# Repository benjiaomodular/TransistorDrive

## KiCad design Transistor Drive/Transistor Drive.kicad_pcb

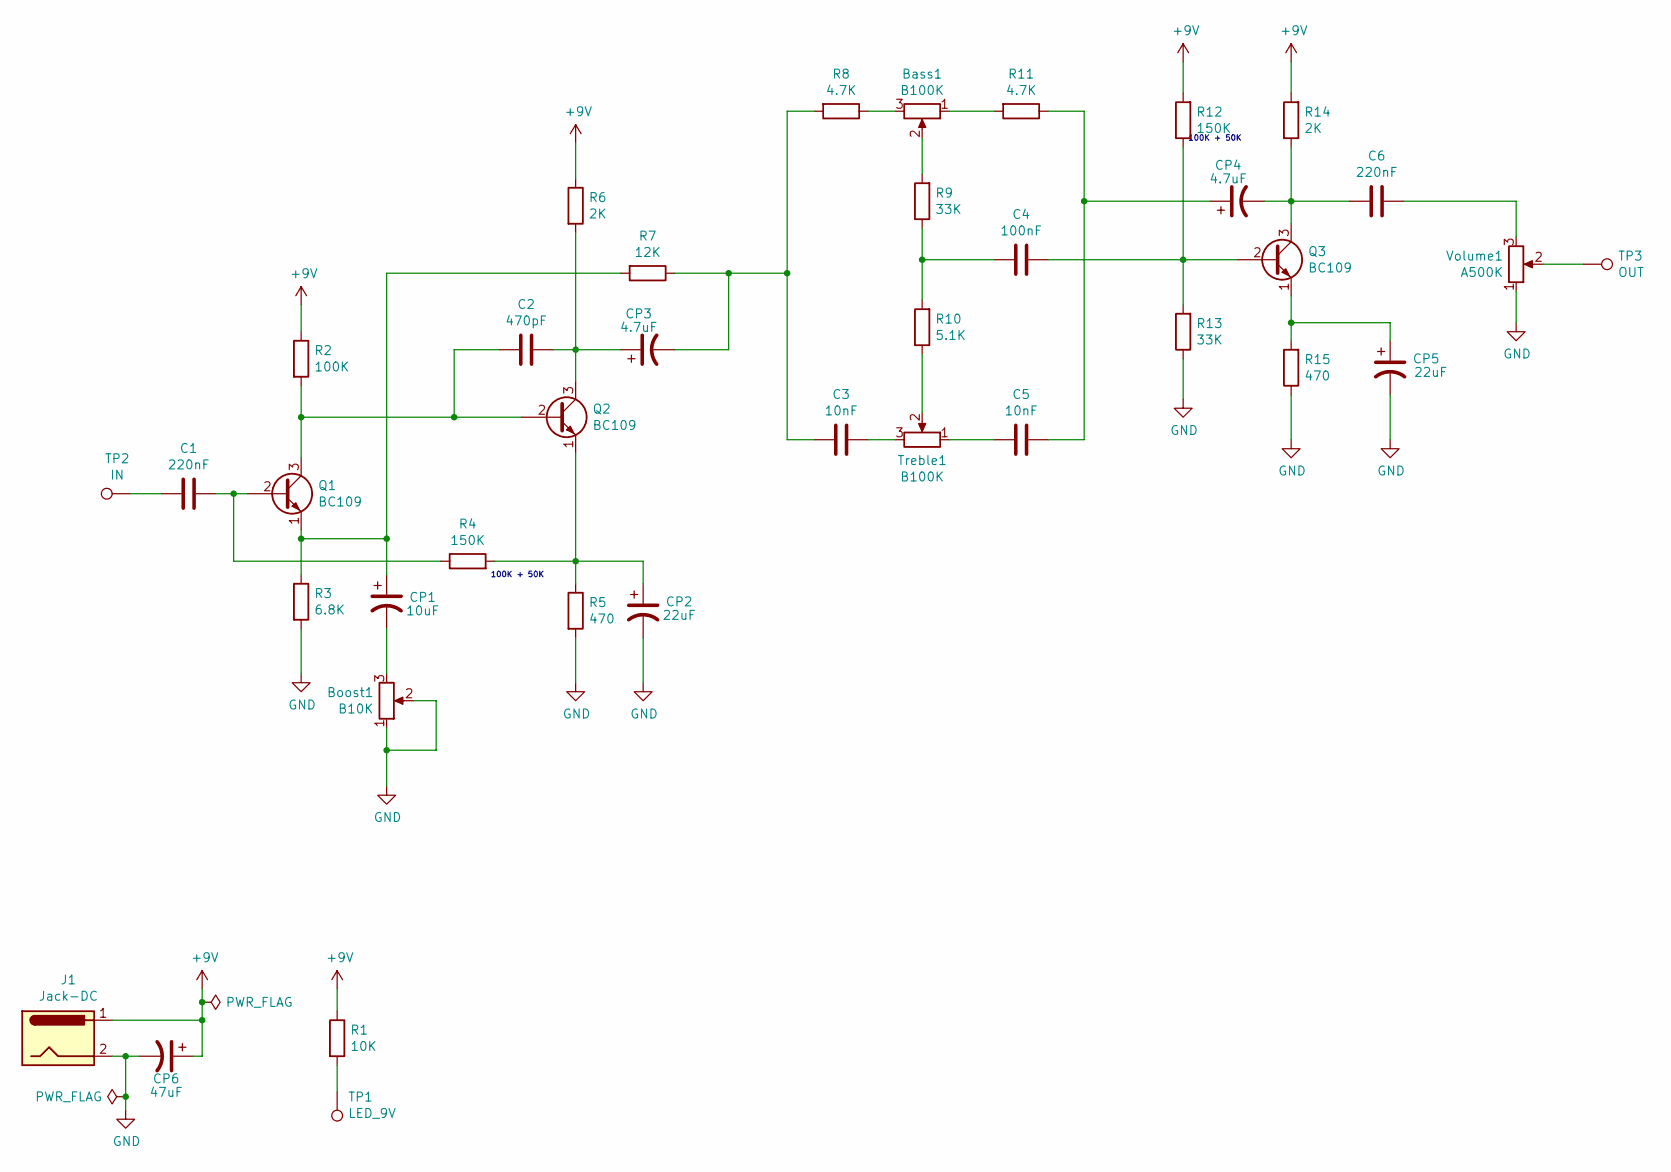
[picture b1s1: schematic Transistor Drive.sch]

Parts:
Bass1: B100K; SolderWire-0.5sqmm_1x03_P4.8mm_D0.9mm_OD2.3mm
Boost1: B10K; SolderWire-0.5sqmm_1x03_P4.8mm_D0.9mm_OD2.3mm
C1, C6: 220nF; C_Rect_L7.2mm_W2.5mm_P5.00mm_FKS2_FKP2_MKS2_MKP2
C2: 470pF; C_Rect_L7.2mm_W2.5mm_P5.00mm_FKS2_FKP2_MKS2_MKP2
C3, C5: 10nF; C_Rect_L7.2mm_W2.5mm_P5.00mm_FKS2_FKP2_MKS2_MKP2
C4: 100nF; C_Rect_L7.2mm_W2.5mm_P5.00mm_FKS2_FKP2_MKS2_MKP2
CP1: 10uF; CP_Radial_D4.0mm_P2.00mm
CP2, CP5: 22uF; CP_Radial_D4.0mm_P2.00mm
CP3, CP4: 4.7uF; CP_Radial_D4.0mm_P2.00mm
CP6: 47uF; CP_Radial_D4.0mm_P2.00mm
J1: Jack-DC; SolderWire-0.5sqmm_1x02_P4.8mm_D0.9mm_OD2.3mm
Q1, Q2, Q3: BC109; TO-18-3
R1: 10K; R_Axial_DIN0207_L6.3mm_D2.5mm_P7.62mm_Horizontal
R2: 100K; R_Axial_DIN0207_L6.3mm_D2.5mm_P7.62mm_Horizontal
R3: 6.8K; R_Axial_DIN0207_L6.3mm_D2.5mm_P7.62mm_Horizontal
R4, R12: 150K; R_Axial_DIN0207_L6.3mm_D2.5mm_P7.62mm_Horizontal
R5, R15: 470; R_Axial_DIN0207_L6.3mm_D2.5mm_P7.62mm_Horizontal
R6, R14: 2K; R_Axial_DIN0207_L6.3mm_D2.5mm_P7.62mm_Horizontal
R7: 12K; R_Axial_DIN0207_L6.3mm_D2.5mm_P7.62mm_Horizontal
R8, R11: 4.7K; R_Axial_DIN0207_L6.3mm_D2.5mm_P7.62mm_Horizontal
R9, R13: 33K; R_Axial_DIN0207_L6.3mm_D2.5mm_P7.62mm_Horizontal
R10: 5.1K; R_Axial_DIN0207_L6.3mm_D2.5mm_P7.62mm_Horizontal
TP1: LED_9V; SolderWire-0.5sqmm_1x01_D0.9mm_OD2.3mm
TP2: IN; SolderWire-0.5sqmm_1x01_D0.9mm_OD2.3mm
TP3: OUT; SolderWire-0.5sqmm_1x01_D0.9mm_OD2.3mm
Treble1: B100K; SolderWire-0.5sqmm_1x03_P4.8mm_D0.9mm_OD2.3mm
Volume1: A500K; SolderWire-0.5sqmm_1x03_P4.8mm_D0.9mm_OD2.3mm

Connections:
+9V: CP6.1, J1.1, R1.1, R2.1, R6.1, R12.2, R14.2
GND: Boost1.1, Boost1.2, CP2.2, CP5.2, CP6.2, J1.2, R3.2, R5.2, R13.1, R15.1, Volume1.1
unnamed: Bass1.1, R11.2
unnamed: Bass1.2, R9.2
unnamed: Bass1.3, R8.1
unnamed: Boost1.3, CP1.2
unnamed: C1.1, Q1.2 (B), R4.1
unnamed: C1.2, TP2.1
unnamed: C2.1, CP3.1, Q2.3 (C), R6.2
unnamed: C2.2, Q1.3 (C), Q2.2 (B), R2.2
unnamed: C3.1, Treble1.3
unnamed: C3.2, CP3.2, R7.1, R8.2
unnamed: C4.1, Q3.2 (B), R12.1, R13.2
unnamed: C4.2, R9.1, R10.2
unnamed: C5.1, CP4.1, R11.1
unnamed: C5.2, Treble1.1
unnamed: C6.1, Volume1.3
unnamed: C6.2, CP4.2, Q3.3 (C), R14.1
unnamed: CP1.1, Q1.1 (E), R3.1, R7.2
unnamed: CP2.1, Q2.1 (E), R4.2, R5.1
unnamed: CP5.1, Q3.1 (E), R15.2
unnamed: R1.2, TP1.1
unnamed: R10.1, Treble1.2
unnamed: TP3.1, Volume1.2

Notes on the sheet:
100K + 50K

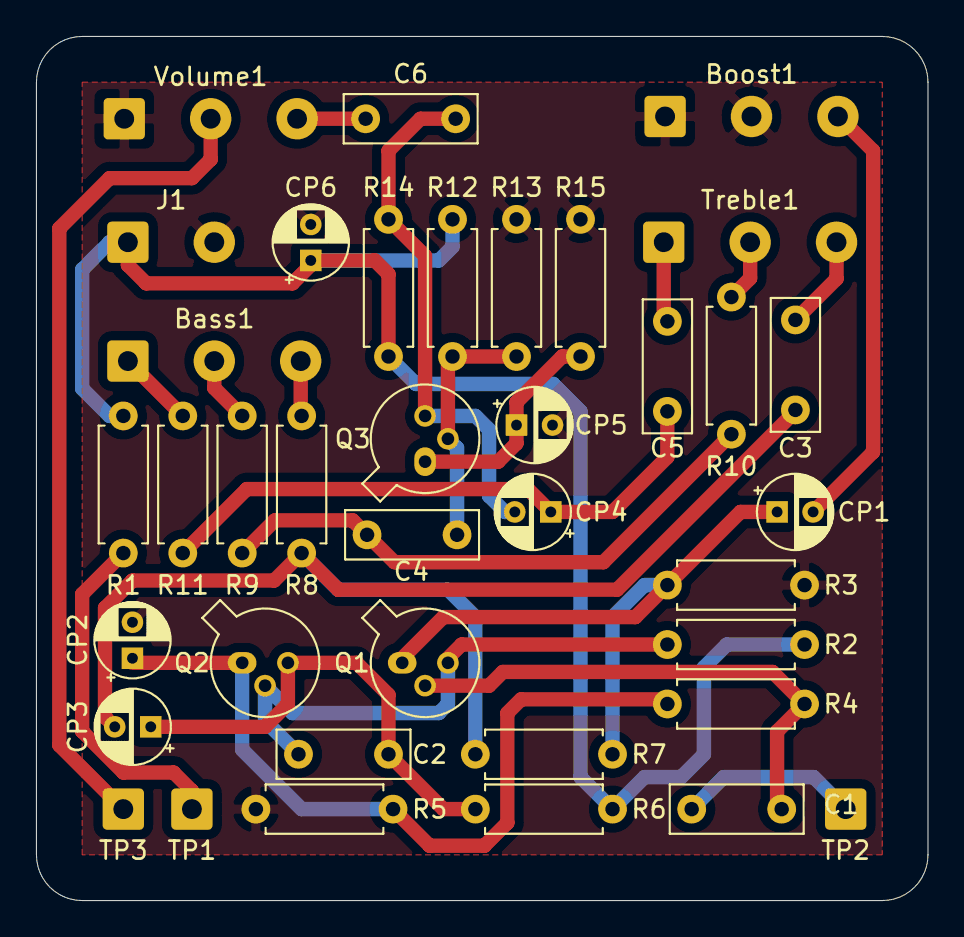
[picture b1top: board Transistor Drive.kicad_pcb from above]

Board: 2 copper layers, 49.5 x 48.0 mm, 38 parts (0 on the bottom side), 24 nets.

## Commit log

2022-02-24 Added more info on the export
